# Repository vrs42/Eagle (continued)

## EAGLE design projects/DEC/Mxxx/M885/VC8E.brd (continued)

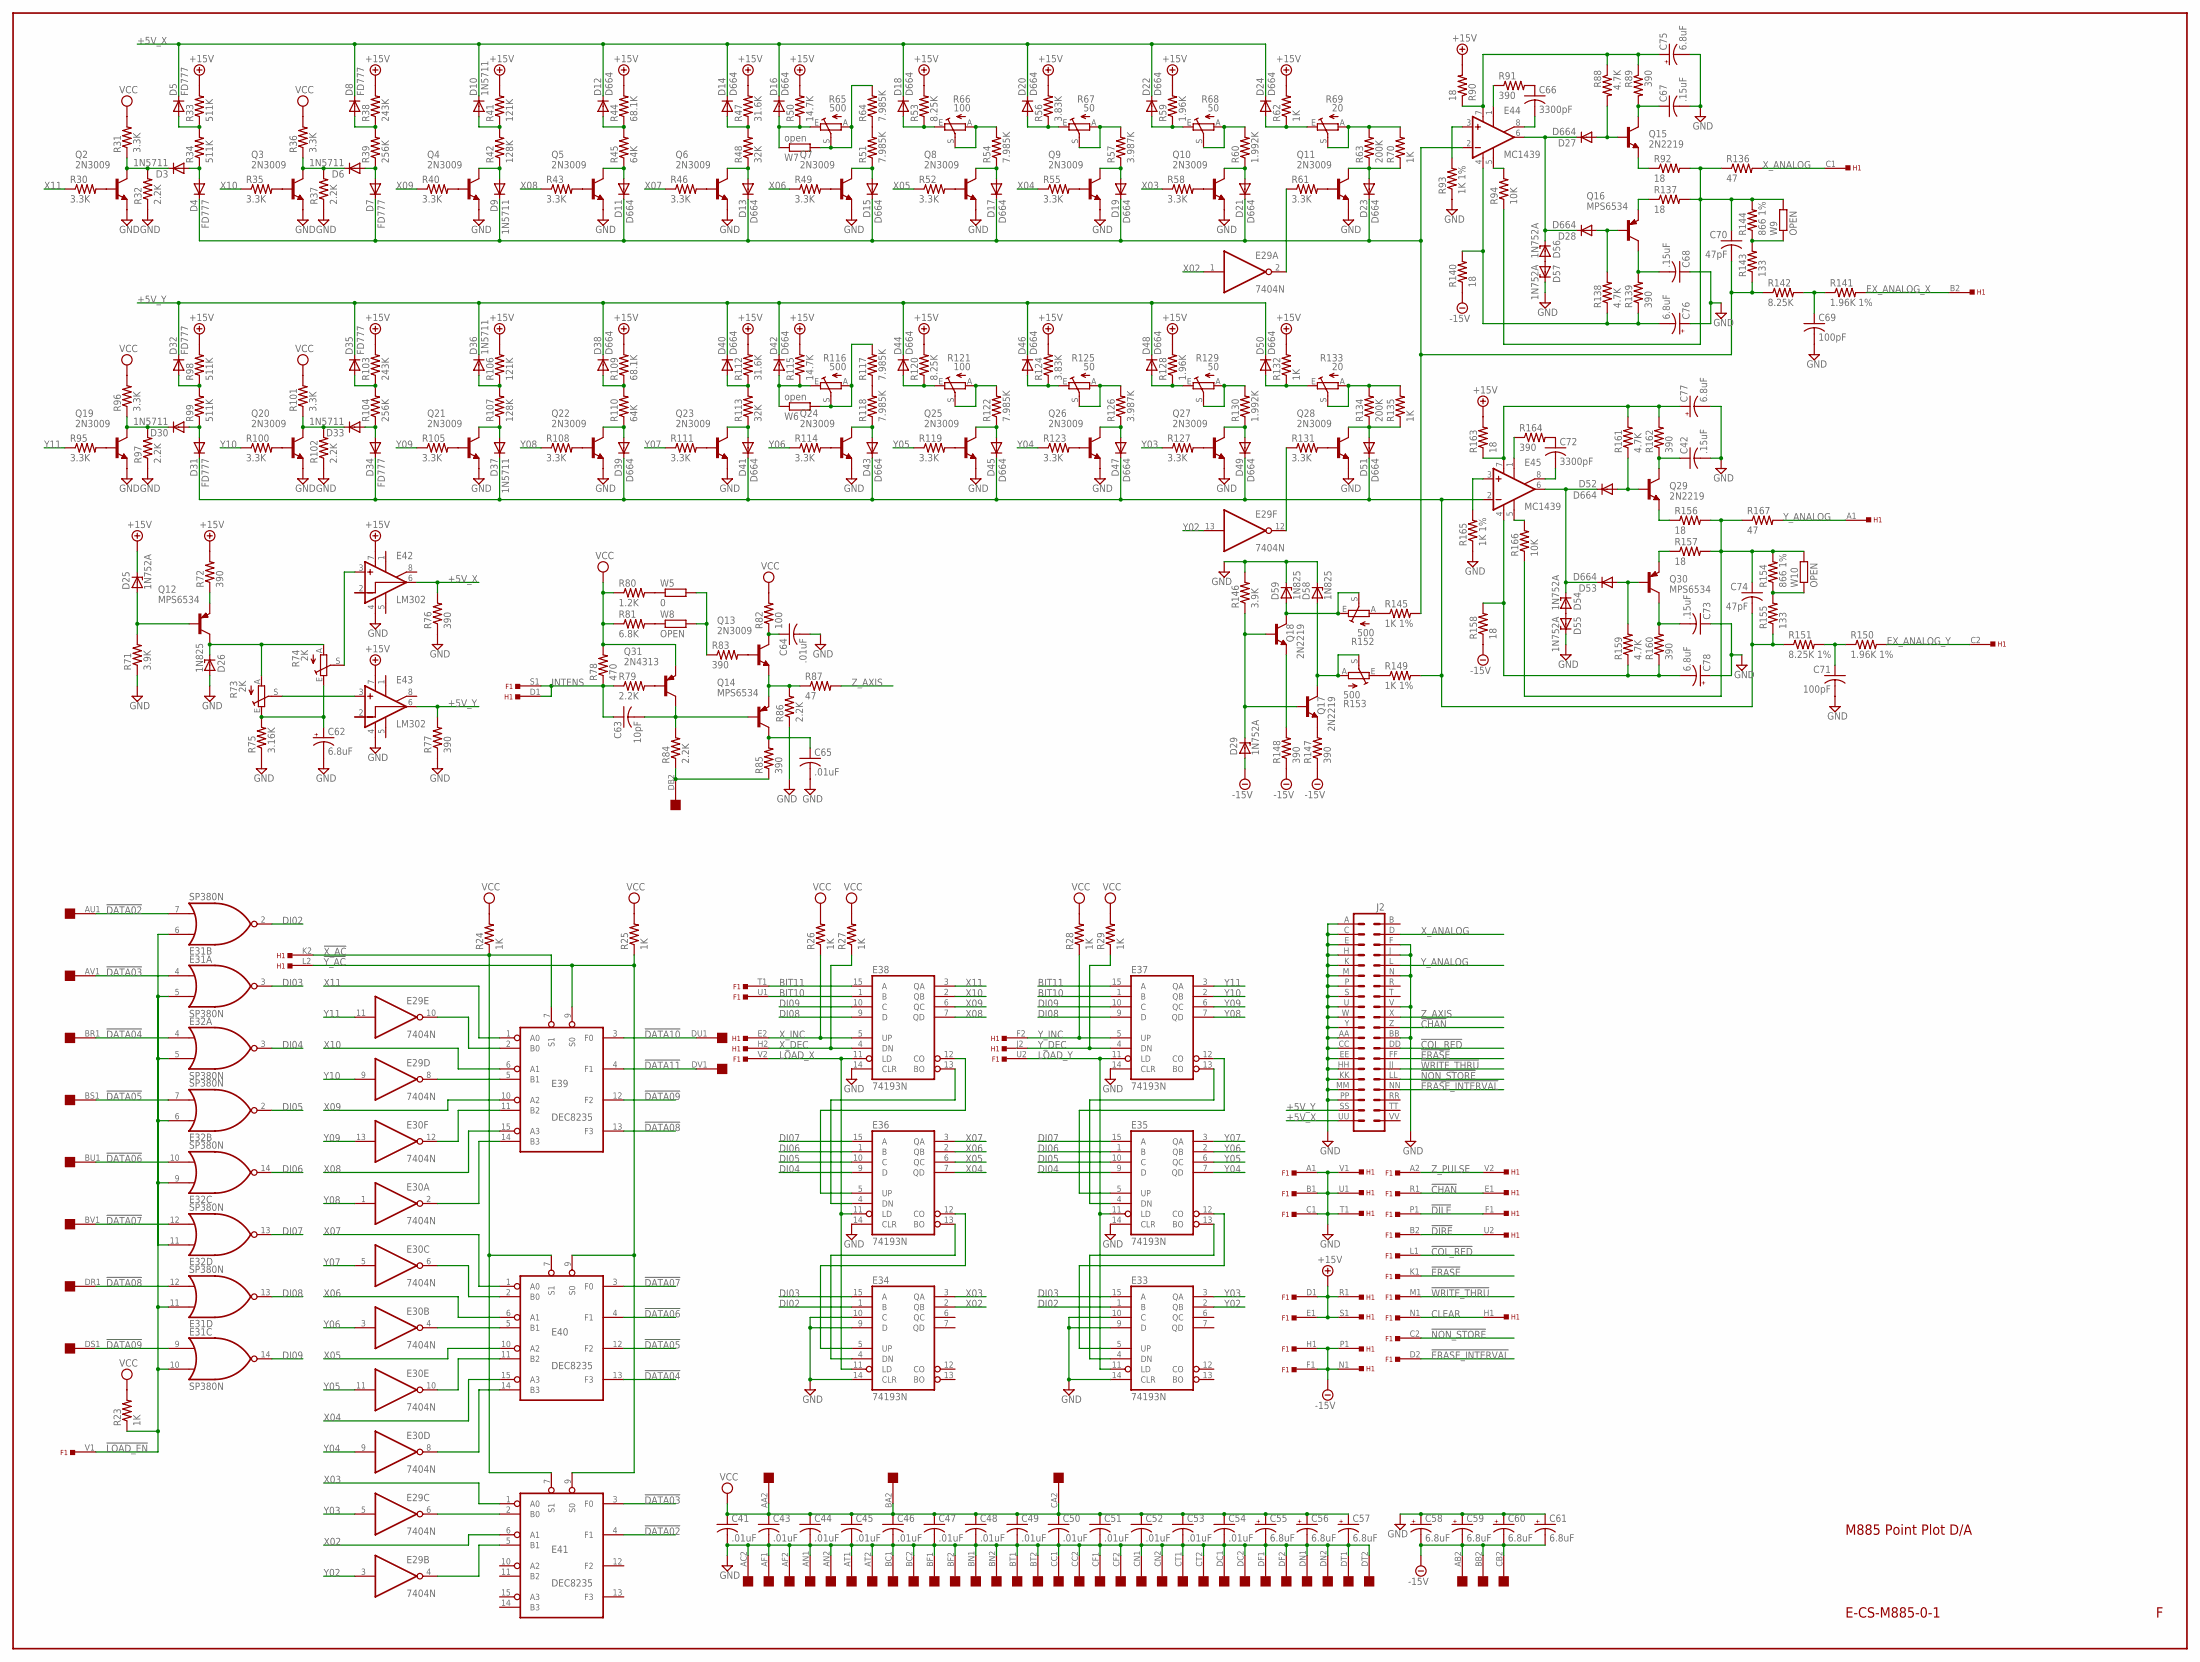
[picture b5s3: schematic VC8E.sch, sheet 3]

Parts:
C41, C43, C44, C45, C46, C47, C48, C49, C50, C51, C52, C53, C54, C64, C65: .01uF; C063-025X075
C42, C67, C68, C73: .15uF; C150-054X183
C55, C56, C57, C58, C59, C60, C61, C62, C75, C76, C77, C78: 6.8uF; E12-8
C63: 10pF; C063-025X075
C66, C72: 3300pF; C150-054X183
C69, C71: 100pF; C063-025X075
C70, C74: 47pF; C063-025X075
D3, D6, D9, D10, D30, D33, D36, D37: 1N5711; DO35-10
D4, D5, D7, D8, D31, D32, D34, D35: FD777; DO35-10
D11, D12, D13, D14, D15, D16, D17, D18, D19, D20, D21, D22, D23, D24, D27, D28, D38, D39, D40, D41, D42, D43, D44, D45, D46, D47, D48, D49, D50, D51, D52, D53: D664; DO35-10
D25, D29, D54, D55, D56, D57: 1N752A; DO35Z10
D26, D58, D59: 1N825; DO35Z10
E29, E30: 7404N; DIL14
E31, E32: SP380N; DIL14
E33, E34, E35, E36, E37, E38: 74193N; DIL16
E39, E40, E41: DEC8235; DIL16
E42, E43: LM302; TO99
E44, E45: MC1439; TO99
F1: EDGE-TOP; EDGE-CON2
H1: EDGE-TOP; EDGE-CON2
J2: DEC40PINH
OMNIBUS1: QUAD; EDGE-CON8
Q2, Q3, Q4, Q5, Q6, Q7, Q8, Q9, Q10, Q11, Q13, Q19, Q20, Q21, Q22, Q23, Q24, Q25, Q26, Q27, Q28: 2N3009; TO5
Q12, Q14, Q16, Q30: MPS6534; TO5
Q15, Q17, Q18, Q29: 2N2219; TO5
Q31: 2N4313; TO5
R23, R24, R25, R26, R27, R28, R29: 1K; 0207/10
R30, R31, R35, R36, R40, R43, R46, R49, R52, R55, R58, R61, R95, R96, R100, R101, R105, R108, R111, R114, R119, R123, R127, R131: 3.3K; 0207/10
R32, R37, R79, R84, R86, R97, R102: 2.2K; 0207/10
R33, R34, R98, R99: 511K; 0207/15
R38, R103: 243K; 0207/15
R39, R104: 256K; 0207/15
R41, R106: 121K; 0207/15
R42, R107: 128K; 0207/15
R44, R109: 68.1K; 0207/15
R45, R110: 64K; 0207/15
R47, R112: 31.6K; 0207/15
R48, R113: 32K; 0207/15
R50, R115: 14.7K; 0207/15
R51, R54, R64, R117, R118, R122: 7.985K; 0207/15
R53, R120, R142: 8.25K; 0207/15
R56, R124: 3.83K; 0207/15
R57, R126: 3.987K; 0207/15
R59, R128: 1.96K; 0207/15
R60, R130: 1.992K; 0207/15
R62, R70, R132, R135: 1K; 0207/15
R63, R134: 200K; 0207/15
R65, R116: 500; S75P
R66, R121: 100; S75P
R67, R68, R125, R129: 50; S75P
R69, R133: 20; S75P
R71, R146: 3.9K; 0207/10
R72, R76, R77, R83, R85, R89, R91, R139, R147, R148, R160, R162, R164: 390; 0207/10
R73, R74: 2K; SP19L
R75: 3.16K; 0207/15
R78: 470; 0207/10
R80: 1.2K; 0207/10
R81: 6.8K; 0207/10
R82: 100; 0207/10
R87, R136, R167: 47; 0207/10
R88, R138, R159, R161: 4.7K; 0207/10
R90, R92, R137, R140, R156, R157, R158, R163: 18; 0207/10
R93, R145, R149, R165: 1K 1%; 0207/15
R94, R166: 10K; 0207/10
R141, R150: 1.96K 1%; 0207/15
R143, R155: 133; 0207/15
R144, R154: 866 1%; 0207/15
R151: 8.25K 1%; 0207/10
R152, R153: 500; SP19L
W5: 0; 0207/10
W6, W7: open; 0207/10
W8, W9, W10: OPEN; 0207/10

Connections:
!CHAN: F1.R1, H1.E1, J2.Z (22); also elsewhere on the board
!COL_RED: F1.L1, J2.DD (26); also elsewhere on the board
!DATA02: E31.7 (I1), E41.4 (F1), OMNIBUS1.AU1
!DATA03: E31.4 (I0), E41.3 (F0), OMNIBUS1.AV1
!DATA04: E32.4 (I0), E40.13 (F3), OMNIBUS1.BR1
!DATA05: E32.7 (I1), E40.12 (F2), OMNIBUS1.BS1
!DATA06: E32.10 (I1), E40.4 (F1), OMNIBUS1.BU1; also elsewhere on the board
!DATA07: E32.12 (I1), E40.3 (F0), OMNIBUS1.BV1; also elsewhere on the board
!DATA08: E31.12 (I1), E39.13 (F3), OMNIBUS1.DR1; also elsewhere on the board
!DATA09: E31.9 (I0), E39.12 (F2), OMNIBUS1.DS1; also elsewhere on the board
!DATA10: E39.3 (F0), OMNIBUS1.DU1; also elsewhere on the board
!DATA11: E39.4 (F1), OMNIBUS1.DV1; also elsewhere on the board
!DILE: F1.P1, H1.F1; also elsewhere on the board
!DIRE: F1.B2, H1.U2; also elsewhere on the board
!ERASE: F1.K1, J2.FF (28); also elsewhere on the board
!ERASE_INTERVAL: F1.D2, J2.NN (34); also elsewhere on the board
!LOAD_EN: E31.5 (I1), E31.6 (I0), E31.10 (I1), E31.11 (I0), E32.5 (I1), E32.6 (I0), E32.9 (I0), E32.11 (I0), F1.V1, R23.1; also elsewhere on the board
!NON_STORE: F1.C2, J2.LL (32); also elsewhere on the board
!WRITE_THRU: F1.M1, J2.JJ (30); also elsewhere on the board
!X_AC: E39.7 (S1), E40.7 (S1), E41.7 (S1), H1.K2, R24.1
!Y_AC: E39.9 (S0), E40.9 (S0), E41.9 (S0), H1.L2, R25.1
+5V_X: D5.C, D8.C, D10.C, D12.C, D14.C, D16.C, D18.C, D20.C, D22.C, D24.C, E42.6 (OUT), J2.UU (39), R76.2
+5V_Y: D32.C, D35.C, D36.C, D38.C, D40.C, D42.C, D44.C, D46.C, D48.C, D50.C, E43.6 (OUT), J2.SS (37), R77.2
+15V: D25.C, E42.7 (V+), E43.7 (V+), F1.D1, F1.E1, H1.R1, H1.S1, R33.2, R38.2, R41.2, R44.2, R47.2, R50.2, R53.2, R56.2, R59.2, R62.2, R72.2, R90.2, R98.2, R103.2, R106.2, R109.2, R112.2, R115.2, R120.2, R124.2, R128.2, R132.2, R163.2; also elsewhere on the board
-15V: C58.-, C59.-, C60.-, C61.-, D29.A, F1.F1, F1.H1, H1.N1, H1.P1, OMNIBUS1.AB2, OMNIBUS1.BB2, OMNIBUS1.CB2, R140.1, R147.1, R148.1, R158.1; also elsewhere on the board
BIT10: E37.1 (B), E38.1 (B), F1.U1; also elsewhere on the board
BIT11: E37.15 (A), E38.15 (A), F1.T1; also elsewhere on the board
CLEAR: F1.N1, H1.H1; also elsewhere on the board
DI02: E31.2 (O), E33.1 (B), E34.1 (B)
DI03: E31.3 (O), E33.15 (A), E34.15 (A)
DI04: E32.3 (O), E35.9 (D), E36.9 (D)
DI05: E32.2 (O), E35.10 (C), E36.10 (C)
DI06: E32.14 (O), E35.1 (B), E36.1 (B)
DI07: E32.13 (O), E35.15 (A), E36.15 (A)
DI08: E31.13 (O), E37.9 (D), E38.9 (D)
DI09: E31.14 (O), E37.10 (C), E38.10 (C)
EX_ANALOG_X: H1.B2, R141.2
EX_ANALOG_Y: H1.C2, R150.2
GND: C41.2, C42.2, C43.2, C44.2, C45.2, C46.2, C47.2, C48.2, C49.2, C50.2, C51.2, C52.2, C53.2, C54.2, C55.-, C56.-, C57.-, C58.+, C59.+, C60.+, C61.+, C62.-, C64.2, C65.2, C67.2, C68.1, C69.2, C71.2, C73.1, C75.-, C76.+, C77.-, C78.+, D26.A, D55.C, D57.C, D58.C, D59.C, E29.7 (GND), E30.7 (GND), E31.1 (GND), E32.1 (GND), E33.8 (GND), E33.9 (D), E33.10 (C), E33.14 (CLR), E34.8 (GND), E34.9 (D), E34.10 (C), E34.14 (CLR), E35.8 (GND), E35.14 (CLR), E36.8 (GND), E36.14 (CLR), E37.8 (GND), E37.14 (CLR), E38.8 (GND), E38.14 (CLR), E39.8 (GND), E40.8 (GND), E41.8 (GND), E42.4 (V-), E43.4 (V-), F1.A1, F1.B1, F1.C1, H1.T1, H1.U1, H1.V1, J2.A (1), J2.AA (23), J2.BB (24), J2.C (3), J2.CC (25), J2.E (5), J2.EE (27), J2.F (6), J2.H (7), J2.HH (29), J2.J (8), J2.K (9), J2.KK (31), J2.M (11), J2.MM (33), J2.N (12), J2.P (13), J2.PP (35), J2.S (15), J2.U (17), J2.V (18), J2.W (19), J2.Y (21), OMNIBUS1.AC2, OMNIBUS1.AF1, OMNIBUS1.AF2, OMNIBUS1.AN1, OMNIBUS1.AN2, OMNIBUS1.AT1, OMNIBUS1.AT2, OMNIBUS1.BC1, OMNIBUS1.BC2, OMNIBUS1.BF1, OMNIBUS1.BF2, OMNIBUS1.BN1, OMNIBUS1.BN2, OMNIBUS1.BT1, OMNIBUS1.BT2, OMNIBUS1.CC1, OMNIBUS1.CC2, OMNIBUS1.CF1, OMNIBUS1.CF2, OMNIBUS1.CN1, OMNIBUS1.CN2, OMNIBUS1.CT1, OMNIBUS1.CT2, OMNIBUS1.DC1, OMNIBUS1.DC2, OMNIBUS1.DF1, OMNIBUS1.DF2, OMNIBUS1.DN1, OMNIBUS1.DN2, OMNIBUS1.DT1, OMNIBUS1.DT2, Q2.1 (E), Q3.1 (E), Q4.1 (E), Q5.1 (E), Q6.1 (E), Q7.1 (E), Q8.1 (E), Q9.1 (E), Q10.1 (E), Q11.1 (E), Q19.1 (E), Q20.1 (E), Q21.1 (E), Q22.1 (E), Q23.1 (E), Q24.1 (E), Q25.1 (E), Q26.1 (E), Q27.1 (E), Q28.1 (E), R32.1, R37.1, R71.1, R75.1, R76.1, R77.1, R86.1, R93.1, R97.1, R102.1, R146.2, R165.1; also elsewhere on the board
INTENS: C63.1, F1.S1, H1.D1, R78.1, R79.1; also elsewhere on the board
LOAD_X: E34.11 (LD), E36.11 (LD), E38.11 (LD), F1.V2; also elsewhere on the board
LOAD_Y: E33.11 (LD), E35.11 (LD), E37.11 (LD), F1.U2; also elsewhere on the board
unnamed: E29.10 (O), E39.2 (B0)
unnamed: E29.8 (O), E39.5 (B1)
unnamed: E30.12 (O), E39.11 (B2)
unnamed: E30.2 (O), E39.14 (B3)
unnamed: E30.6 (O), E40.2 (B0)
unnamed: E30.4 (O), E40.5 (B1)
unnamed: E30.10 (O), E40.11 (B2)
unnamed: E30.8 (O), E40.14 (B3)
unnamed: E29.6 (O), E41.2 (B0)
unnamed: E29.4 (O), E41.5 (B1)
unnamed: E34.4 (DN), E36.13 (BO)
unnamed: E34.5 (UP), E36.12 (CO)
unnamed: E36.4 (DN), E38.13 (BO)
unnamed: E36.5 (UP), E38.12 (CO)
unnamed: E33.4 (DN), E35.13 (BO)
unnamed: E33.5 (UP), E35.12 (CO)
unnamed: E35.4 (DN), E37.13 (BO)
unnamed: E35.5 (UP), E37.12 (CO)
unnamed: D5.A, R33.1, R34.2
unnamed: D3.A, D4.A, R34.1
unnamed: Q2.2 (B), R30.2
unnamed: D3.C, Q2.3 (C), R31.1, R32.2
unnamed: D8.A, R38.1, R39.2
unnamed: D6.A, D7.A, R39.1
unnamed: Q3.2 (B), R35.2
unnamed: D6.C, Q3.3 (C), R36.1, R37.2
unnamed: D10.A, R41.1, R42.2
unnamed: D9.A, Q4.3 (C), R42.1
unnamed: Q4.2 (B), R40.2
unnamed: D12.A, R44.1, R45.2
unnamed: D11.A, Q5.3 (C), R45.1
unnamed: Q5.2 (B), R43.2
unnamed: D14.A, R47.1, R48.2
unnamed: D13.A, Q6.3 (C), R48.1
unnamed: Q6.2 (B), R46.2
unnamed: D15.A, Q7.3 (C), R51.1
unnamed: Q7.2 (B), R49.2
unnamed: D18.A, R53.1, R66.E
unnamed: D17.A, Q8.3 (C), R54.1
unnamed: Q8.2 (B), R52.2
unnamed: R57.2, R67.A, R67.S
unnamed: D19.A, Q9.3 (C), R57.1
unnamed: Q9.2 (B), R55.2
unnamed: D22.A, R59.1, R68.E
unnamed: D21.A, Q10.3 (C), R60.1
unnamed: Q10.2 (B), R58.2
unnamed: D24.A, R62.1, R69.E
unnamed: D23.A, Q11.3 (C), R63.1, R70.1
unnamed: Q11.2 (B), R61.2
unnamed: E29.2 (O), R61.1
unnamed: D16.A, R50.1, R65.E, W7.1
unnamed: R51.2, R64.1
unnamed: R64.2, R65.A, R65.S, W7.2
unnamed: R54.2, R66.A, R66.S
unnamed: D20.A, R56.1, R67.E
unnamed: R60.2, R68.A, R68.S
unnamed: R63.2, R69.A, R69.S, R70.2
unnamed: D32.A, R98.1, R99.2
unnamed: D30.A, D31.A, R99.1
unnamed: Q19.2 (B), R95.2
unnamed: D30.C, Q19.3 (C), R96.1, R97.2
unnamed: D35.A, R103.1, R104.2
unnamed: D33.A, D34.A, R104.1
unnamed: C74.2, D31.C, D34.C, D37.C, D39.C, D41.C, D43.C, D45.C, D47.C, D49.C, D51.C, E45.2 (-IN), R149.2, R151.1, R155.1
unnamed: Q20.2 (B), R100.2
unnamed: D33.C, Q20.3 (C), R101.1, R102.2
unnamed: D36.A, R106.1, R107.2
unnamed: D37.A, Q21.3 (C), R107.1
unnamed: Q21.2 (B), R105.2
unnamed: D38.A, R109.1, R110.2
unnamed: D39.A, Q22.3 (C), R110.1
unnamed: Q22.2 (B), R108.2
unnamed: D40.A, R112.1, R113.2
unnamed: D41.A, Q23.3 (C), R113.1
unnamed: Q23.2 (B), R111.2
unnamed: D43.A, Q24.3 (C), R118.1
unnamed: Q24.2 (B), R114.2
unnamed: D44.A, R120.1, R121.E
unnamed: D45.A, Q25.3 (C), R122.1
unnamed: Q25.2 (B), R119.2
unnamed: R125.A, R125.S, R126.2
unnamed: D47.A, Q26.3 (C), R126.1
unnamed: Q26.2 (B), R123.2
unnamed: D48.A, R128.1, R129.E
unnamed: D49.A, Q27.3 (C), R130.1
unnamed: Q27.2 (B), R127.2
unnamed: D50.A, R132.1, R133.E
unnamed: D51.A, Q28.3 (C), R134.1, R135.1
unnamed: Q28.2 (B), R131.2
unnamed: E29.12 (O), R131.1
unnamed: D42.A, R115.1, R116.E, W6.1
unnamed: R117.1, R118.2
unnamed: R116.A, R116.S, R117.2, W6.2
unnamed: R121.A, R121.S, R122.2
unnamed: D46.A, R124.1, R125.E
unnamed: R129.A, R129.S, R130.2
unnamed: R133.A, R133.S, R134.2, R135.2
unnamed: D25.A, Q12.2 (B), R71.2
unnamed: Q12.1 (E), R72.1
unnamed: D26.C, Q12.3 (C), R73.A, R74.A
unnamed: C62.+, R73.E, R74.E, R75.2
unnamed: E43.3 (+IN), R73.S
unnamed: E42.3 (+IN), R74.S
unnamed: Q31.2 (B), R79.2
unnamed: C63.2, Q14.2 (B), Q31.3 (C), R84.2
unnamed: OMNIBUS1.DB2, R84.1, R85.1
unnamed: C65.1, Q14.3 (C), R85.2
unnamed: Q13.1 (E), Q14.1 (E), R86.2, R87.1
unnamed: R80.2, W5.1
unnamed: R81.2, W8.1
unnamed: Q13.2 (B), R83.2
unnamed: R83.1, W5.2, W8.2
unnamed: C64.1, Q13.3 (C), R82.1
unnamed: C75.+, E44.7 (V+), R88.1, R89.1, R90.1
unnamed: C66.1, R91.2
unnamed: C66.2, E44.8 (ON2)
unnamed: E44.1 (ON1), R91.1
unnamed: D27.C, D28.C, D56.C, E44.6 (OUT)
unnamed: D56.A, D57.A
unnamed: D27.A, Q15.2 (B), R88.2
unnamed: C67.1, Q15.3 (C), R89.2
unnamed: D28.A, Q16.2 (B), R138.2
unnamed: C68.2, Q16.3 (C), R139.2
unnamed: C76.-, E44.4 (V-), R138.1, R139.1, R140.2
unnamed: E44.5 (OPT), R94.2
unnamed: C70.1, R92.2, R94.1, R136.1, R137.2, R144.2, W9.2
unnamed: Q16.1 (E), R137.1
unnamed: Q15.1 (E), R92.1
unnamed: E44.3 (+IN), R93.2
unnamed: R143.2, R144.1, W9.1
unnamed: C70.2, D4.C, D7.C, D9.C, D11.C, D13.C, D15.C, D17.C, D19.C, D21.C, D23.C, E44.2 (-IN), R142.1, R143.1, R145.2
unnamed: C69.1, R141.1, R142.2
unnamed: R145.1, R152.A
unnamed: D29.C, Q17.2 (B), Q18.2 (B), R146.1
unnamed: Q18.1 (E), R148.2
unnamed: Q17.1 (E), R147.2
unnamed: D59.A, Q18.3 (C), R152.E, R152.S
unnamed: D58.A, Q17.3 (C), R153.A, R153.S
unnamed: R149.1, R153.E
unnamed: C77.+, E45.7 (V+), R161.2, R162.2, R163.1
unnamed: C72.2, E45.8 (ON2)
unnamed: E45.1 (ON1), R164.1
unnamed: D52.C, D53.C, D54.C, E45.6 (OUT)
unnamed: D52.A, Q29.2 (B), R161.1
unnamed: C42.1, Q29.3 (C), R162.1
unnamed: D53.A, Q30.2 (B), R159.2
unnamed: C73.2, Q30.3 (C), R160.2
unnamed: C78.-, E45.4 (V-), R158.2, R159.1, R160.1
unnamed: E45.5 (OPT), R166.2
unnamed: C74.1, R154.2, R156.2, R157.2, R166.1, R167.1, W10.2
unnamed: Q30.1 (E), R157.1
unnamed: Q29.1 (E), R156.1
unnamed: E45.3 (+IN), R165.2
unnamed: R154.1, R155.2, W10.1
unnamed: C71.1, R150.1, R151.2
unnamed: D54.A, D55.A
unnamed: C72.1, R164.2
VCC: C41.1, C43.1, C44.1, C45.1, C46.1, C47.1, C48.1, C49.1, C50.1, C51.1, C52.1, C53.1, C54.1, C55.+, C56.+, C57.+, E29.14 (VCC), E30.14 (VCC), E31.8 (VCC), E32.8 (VCC), E33.16 (VCC), E34.16 (VCC), E35.16 (VCC), E36.16 (VCC), E37.16 (VCC), E38.16 (VCC), E39.16 (VCC), E40.16 (VCC), E41.16 (VCC), OMNIBUS1.AA2, OMNIBUS1.BA2, OMNIBUS1.CA2, Q31.1 (E), R23.2, R24.2, R25.2, R26.2, R27.2, R28.2, R29.2, R31.2, R36.2, R78.2, R80.1, R81.1, R82.2, R96.2, R101.2; also elsewhere on the board
X02: E29.1 (I), E34.2 (QB), E41.6 (A1)
X03: E34.3 (QA), E41.1 (A0), R58.1
X04: E36.7 (QD), E40.15 (A3), R55.1
X05: E36.6 (QC), E40.10 (A2), R52.1
X06: E36.2 (QB), E40.6 (A1), R49.1
X07: E36.3 (QA), E40.1 (A0), R46.1
X08: E38.7 (QD), E39.15 (A3), R43.1
X09: E38.6 (QC), E39.10 (A2), R40.1
X10: E38.2 (QB), E39.6 (A1), R35.1
X11: E38.3 (QA), E39.1 (A0), R30.1
X_ANALOG: H1.C1, J2.D (4), R136.2
X_DEC: E38.4 (DN), H1.H2, R27.1
X_INC: E38.5 (UP), H1.E2, R26.1
Y02: E29.3 (I), E29.13 (I), E33.2 (QB)
Y03: E29.5 (I), E33.3 (QA), R127.1
Y04: E30.9 (I), E35.7 (QD), R123.1
Y05: E30.11 (I), E35.6 (QC), R119.1
Y06: E30.3 (I), E35.2 (QB), R114.1
Y07: E30.5 (I), E35.3 (QA), R111.1
Y08: E30.1 (I), E37.7 (QD), R108.1
Y09: E30.13 (I), E37.6 (QC), R105.1
Y10: E29.9 (I), E37.2 (QB), R100.1
Y11: E29.11 (I), E37.3 (QA), R95.1
Y_ANALOG: H1.A1, J2.L (10), R167.2
Y_DEC: E37.4 (DN), H1.J2, R29.1
Y_INC: E37.5 (UP), H1.F2, R28.1
Z_AXIS: J2.X (20), R87.2
Z_PULSE: F1.A2, H1.V2; also elsewhere on the board

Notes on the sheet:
E-CS-M885-0-1
M885 Point Plot D/A

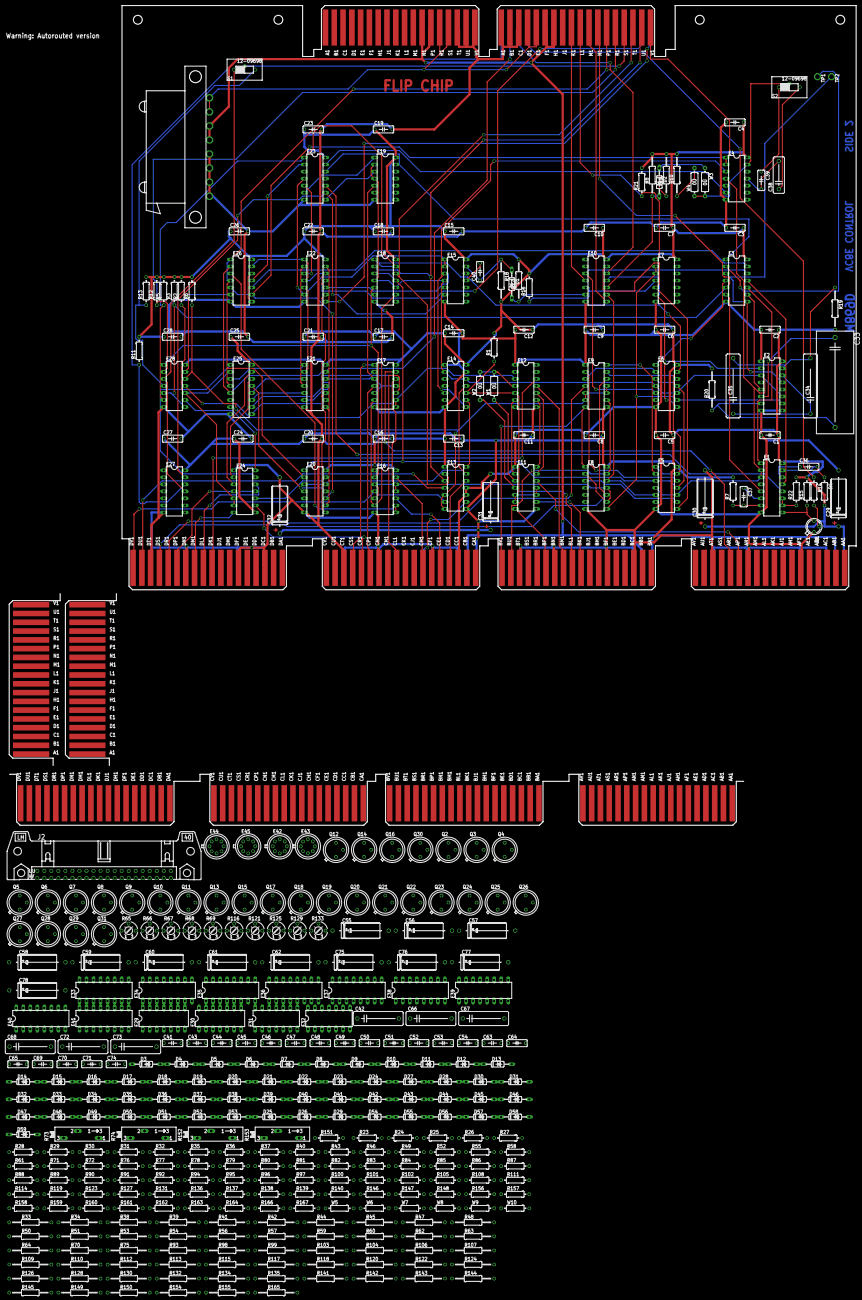
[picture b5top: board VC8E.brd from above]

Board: 4 copper layers, 306.1 x 296.2 mm, 402 parts (0 on the bottom side), 334 nets.

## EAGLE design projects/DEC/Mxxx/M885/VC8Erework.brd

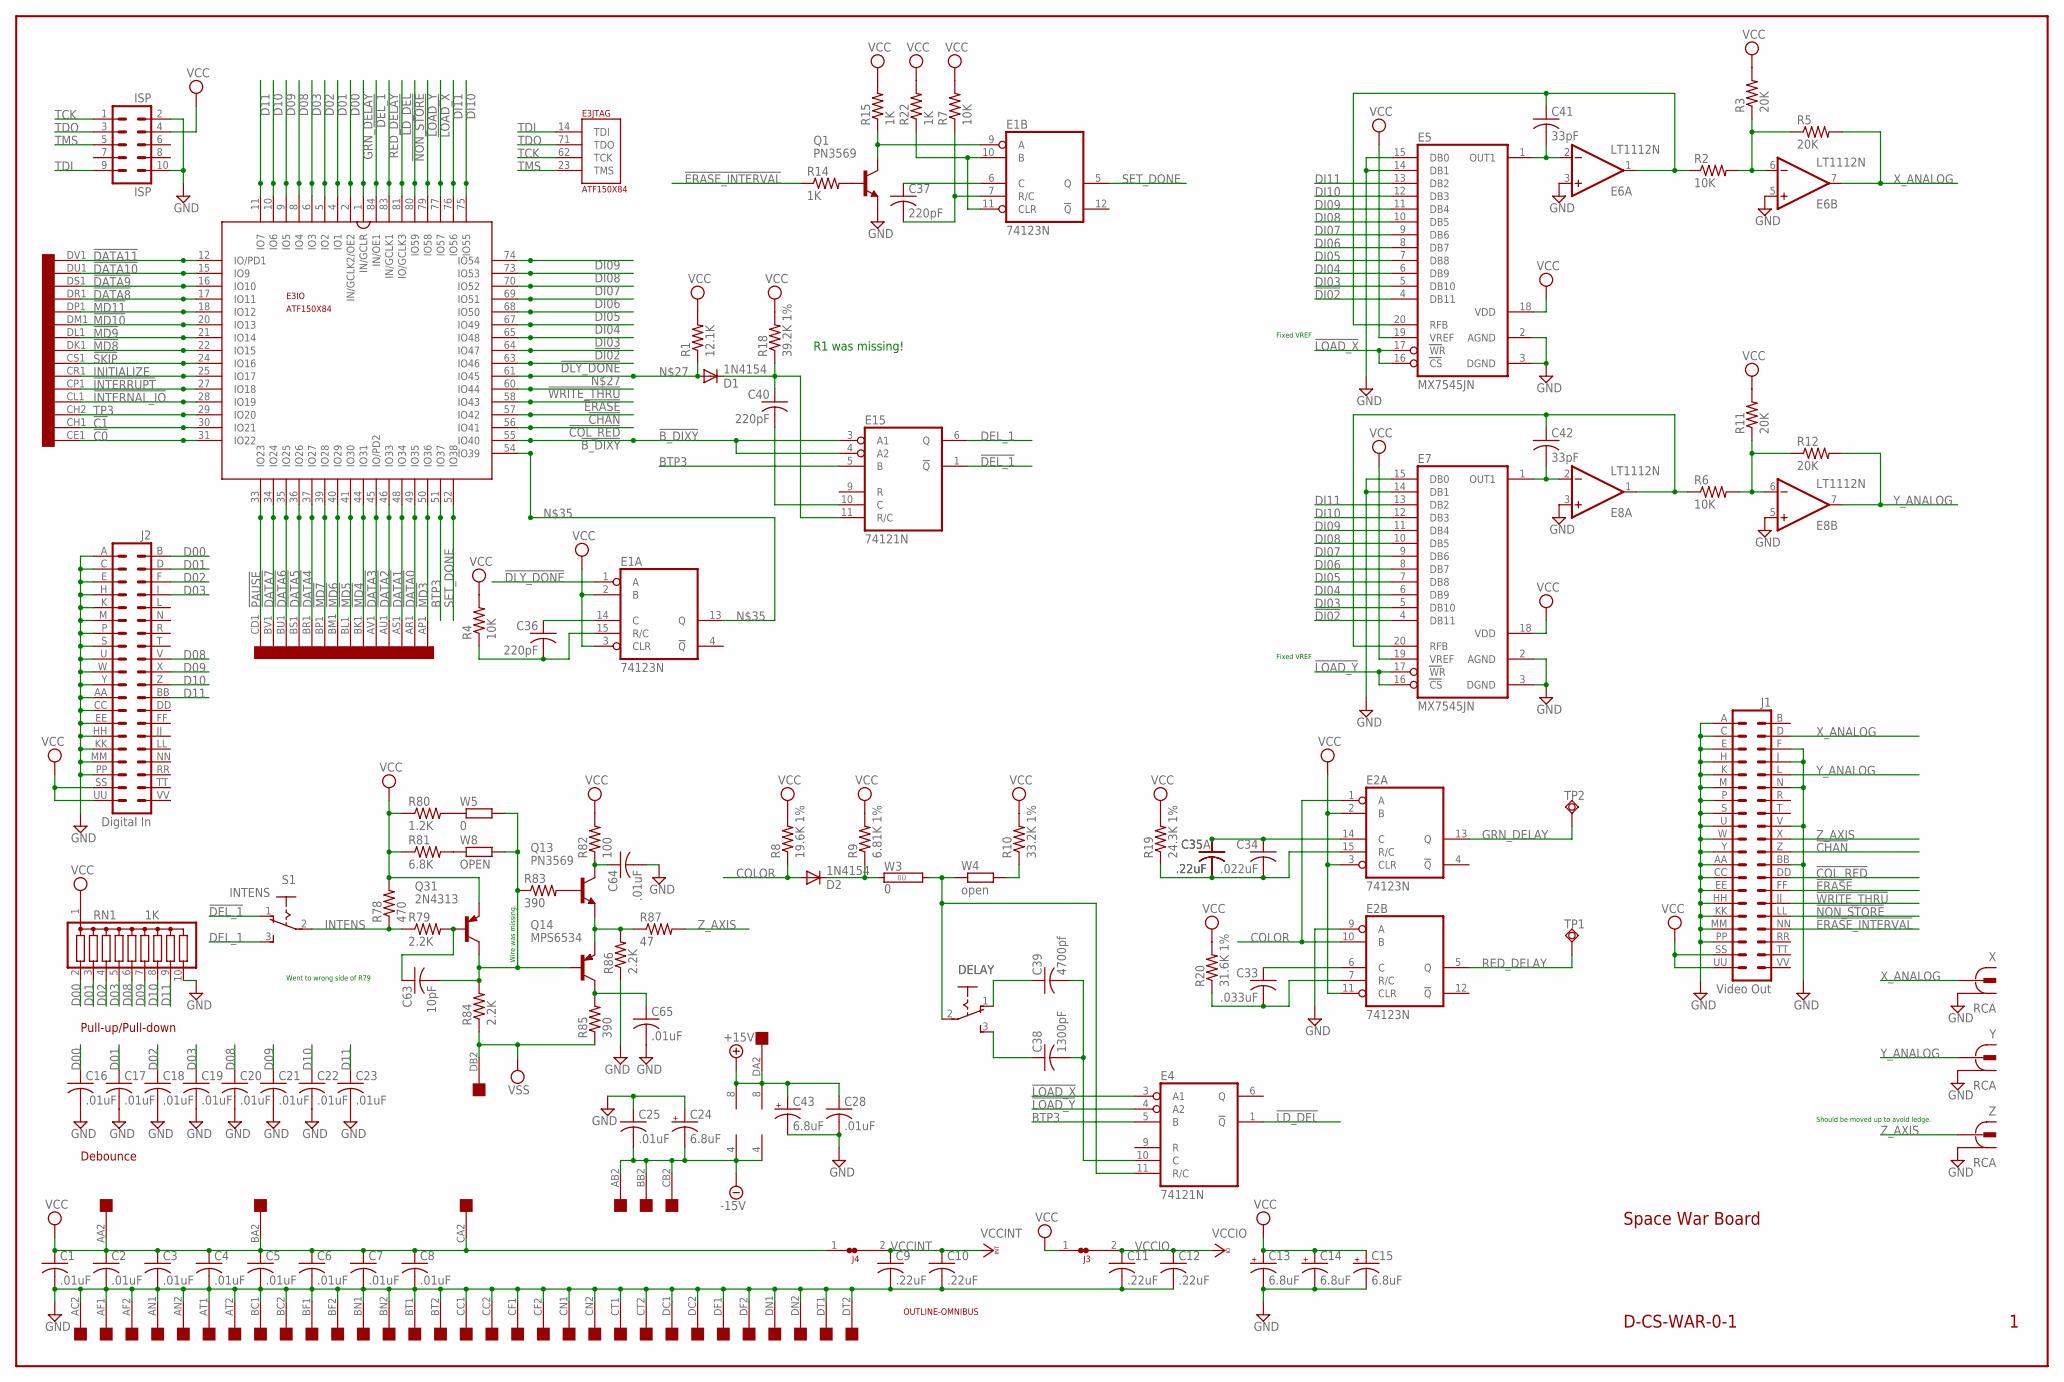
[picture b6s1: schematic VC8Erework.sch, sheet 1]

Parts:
C1, C2, C3, C4, C5, C6, C7, C8, C16, C17, C18, C19, C20, C21, C22, C23, C25, C28, C64, C65: .01uF; C063-025X075
C9, C10, C11, C12: .22uF; C063-025X075
C13, C14, C15, C24, C43: 6.8uF; E12-8
C33: .033uF; C102-043X133
C34: .022uF; C102-043X133
C35: .22uF; C050-025X075
C35A: .22uF; C102-043X133
C36, C37, C40: 220pF; C063-025X075
C38: 1300pF; C150-054X183
C39: 4700pf; C102-043X133
C41, C42: 33pF; C063-025X075
C63: 10pF; C063-025X075
D1, D2: 1N4154; DO35-10
DELAY: DELAY; M251
E1, E2: 74123N; DIL16
E3: ATF150X84; S84
E4, E15: 74121N; DIL14
E5, E7: MX7545JN; DIL20
E6, E8: LT1112N; DIL08
ISP: ISP; ML10
J1: Video Out; DEC40PINH
J2: Digital In; DEC40PINH
J3, J4: JUMPER-NC1; NC1
OMNIBUS: QUAD; EDGE-CON8
Q1: PN3569; TO18-
Q13: PN3569; TO5
Q14: MPS6534; TO5
Q31: 2N4313; TO5
R1: 12.1K; 0207/7
R2, R4, R6, R7: 10K; 0207/10
R3, R5, R11, R12: 20K; 0207/10
R8: 19.6K 1%; 0207/15
R9: 6.81K 1%; 0207/15
R10: 33.2K 1%; 0207/15
R14, R15, R22: 1K; 0207/10
R18: 39.2K 1%; 0207/15
R19: 24.3K 1%; 0207/15
R20: 31.6K 1%; 0207/15
R78: 470; 0207/10
R79, R84, R86: 2.2K; 0207/10
R80: 1.2K; 0207/10
R81: 6.8K; 0207/10
R82: 100; 0207/10
R83, R85: 390; 0207/10
R87: 47; 0207/10
RN1: 1K; SIL10
S1: INTENS; M251
TP1, TP2: TPSQPAD1-17; P1-17
U$1: OUTLINE-OMNIBUS; OMNIBUS
W3: 0; 0R/10
W4: open; 0207/10
W5: 0; 0207/10
W8: OPEN; 0207/10
X: RCA
Y: RCA
Z: RCA

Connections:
!B_DIXY: E3.55 (IO40), E15.3 (A1), E15.4 (A2)
!C0: E3.31 (IO22), OMNIBUS.CE1
!C1: E3.30 (IO21), OMNIBUS.CH1
!CHAN: E3.57 (IO42), J1.Z (22)
!COL_RED: E3.56 (IO41), J1.DD (26)
!DATA0: E3.49 (IO35), OMNIBUS.AR1
!DATA1: E3.48 (IO34), OMNIBUS.AS1
!DATA2: E3.46 (IO33), OMNIBUS.AU1
!DATA3: E3.45 (IO/PD2), OMNIBUS.AV1
!DATA4: E3.37 (IO27), OMNIBUS.BR1
!DATA5: E3.36 (IO26), OMNIBUS.BS1
!DATA6: E3.35 (IO25), OMNIBUS.BU1
!DATA7: E3.34 (IO24), OMNIBUS.BV1
!DATA8: E3.17 (IO11), OMNIBUS.DR1
!DATA9: E3.16 (IO10), OMNIBUS.DS1
!DATA10: E3.15 (IO9), OMNIBUS.DU1
!DATA11: E3.12 (IO/PD1), OMNIBUS.DV1
!DEL_1: E3.84 (IN/OE1), E15.1 (!Q), S1.1 (O)
!DI02: E3.64 (IO47), E5.4 (DB11), E7.4 (DB11)
!DLY_DONE: E1.1 (A), E3.63 (IO46)
!ERASE: E3.58 (IO43), J1.FF (28)
!ERASE_INTERVAL: J1.NN (34), R14.1
!INTERNAL_IO: E3.28 (IO19), OMNIBUS.CL1
!INTERRUPT: E3.27 (IO18), OMNIBUS.CP1
!LD_DEL: E3.81 (IO/GCLK3), E4.1 (!Q)
!LOAD_X: E3.77 (IO57), E4.3 (A1), E5.16 (CS), E5.17 (WR)
!LOAD_Y: E3.79 (IO58), E4.4 (A2), E7.16 (CS), E7.17 (WR)
!MD3: E3.50 (IO36), OMNIBUS.AP1
!MD4: E3.44 (IO31), OMNIBUS.BK1
!MD5: E3.41 (IO30), OMNIBUS.BL1
!MD6: E3.40 (IO29), OMNIBUS.BM1
!MD7: E3.39 (IO28), OMNIBUS.BP1
!MD8: E3.22 (IO15), OMNIBUS.DK1
!MD9: E3.21 (IO14), OMNIBUS.DL1
!MD10: E3.20 (IO13), OMNIBUS.DM1
!MD11: E3.18 (IO12), OMNIBUS.DP1
!NON_STORE: E3.80 (IO59), J1.LL (32)
!PAUSE: E3.33 (IO23), OMNIBUS.CD1
!SKIP: E3.24 (IO16), OMNIBUS.CS1
!WRITE_THRU: E3.60 (IO44), J1.JJ (30)
+15V: C28.1, C43.+, E6.8 (V+), E8.8 (V+), OMNIBUS.DA2
-15V: C24.-, C25.2, E6.4 (V-), E8.4 (V-), OMNIBUS.AB2, OMNIBUS.BB2, OMNIBUS.CB2
BTP3: E3.51 (IO37), E4.5 (B), E15.5 (B)
COLOR: D2.A, E2.1 (A), E2.10 (B), R8.1
D00: C16.1, E3.2 (IN/GCLK2/OE2), J2.B (2), RN1.2
D01: C17.1, E3.4 (IO1), J2.D (4), RN1.3
D02: C18.1, E3.5 (IO2), J2.F (6), RN1.4
D03: C19.1, E3.6 (IO3), J2.J (8), RN1.5
D08: C20.1, E3.8 (IO4), J2.V (18), RN1.6
D09: C21.1, E3.9 (IO5), J2.X (20), RN1.7
D10: C22.1, E3.10 (IO6), J2.Z (22), RN1.8
D11: C23.1, E3.11 (IO7), J2.BB (24), RN1.9
DEL_1: E15.6 (Q), S1.3 (S)
DI03: E3.65 (IO48), E5.5 (DB10), E7.5 (DB10)
DI04: E3.67 (IO49), E5.6 (DB9), E7.6 (DB9)
DI05: E3.68 (IO50), E5.7 (DB8), E7.7 (DB8)
DI06: E3.69 (IO51), E5.8 (DB7), E7.8 (DB7)
DI07: E3.70 (IO52), E5.9 (DB6), E7.9 (DB6)
DI08: E3.73 (IO53), E5.10 (DB5), E7.10 (DB5)
DI09: E3.74 (IO54), E5.11 (DB4), E7.11 (DB4)
DI10: E3.75 (IO55), E5.12 (DB3), E7.12 (DB3)
DI11: E3.76 (IO56), E5.13 (DB2), E7.13 (DB2)
GND: C1.2, C2.2, C3.2, C4.2, C5.2, C6.2, C7.2, C8.2, C9.2, C10.2, C11.2, C12.2, C13.-, C14.-, C15.-, C16.2, C17.2, C18.2, C19.2, C20.2, C21.2, C22.2, C23.2, C24.+, C25.1, C28.2, C43.-, C64.2, C65.2, E1.8 (GND), E2.8 (GND), E2.9 (A), E3.7 (GND), E3.19 (GND), E3.32 (GND), E3.42 (GND), E3.47 (GND), E3.59 (GND), E3.72 (GND), E3.82 (GND), E4.7 (GND), E5.2 (AGND), E5.3 (DGND), E5.14 (DB1), E5.15 (DB0), E6.3 (+IN), E6.5 (+IN), E7.2 (AGND), E7.3 (DGND), E7.14 (DB1), E7.15 (DB0), E8.3 (+IN), E8.5 (+IN), E15.7 (GND), ISP.2, ISP.10, J1.A (1), J1.AA (23), J1.BB (24), J1.C (3), J1.CC (25), J1.E (5), J1.EE (27), J1.F (6), J1.H (7), J1.HH (29), J1.J (8), J1.K (9), J1.KK (31), J1.M (11), J1.MM (33), J1.N (12), J1.P (13), J1.PP (35), J1.S (15), J1.U (17), J1.V (18), J1.W (19), J1.Y (21), J2.A (1), J2.AA (23), J2.C (3), J2.CC (25), J2.E (5), J2.EE (27), J2.H (7), J2.HH (29), J2.K (9), J2.KK (31), J2.M (11), J2.MM (33), J2.P (13), J2.PP (35), J2.S (15), J2.U (17), J2.W (19), J2.Y (21), OMNIBUS.AC2, OMNIBUS.AF1, OMNIBUS.AF2, OMNIBUS.AN1, OMNIBUS.AN2, OMNIBUS.AT1, OMNIBUS.AT2, OMNIBUS.BC1, OMNIBUS.BC2, OMNIBUS.BF1, OMNIBUS.BF2, OMNIBUS.BN1, OMNIBUS.BN2, OMNIBUS.BT1, OMNIBUS.BT2, OMNIBUS.CC1, OMNIBUS.CC2, OMNIBUS.CF1, OMNIBUS.CF2, OMNIBUS.CN1, OMNIBUS.CN2, OMNIBUS.CT1, OMNIBUS.CT2, OMNIBUS.DC1, OMNIBUS.DC2, OMNIBUS.DF1, OMNIBUS.DF2, OMNIBUS.DN1, OMNIBUS.DN2, OMNIBUS.DT1, OMNIBUS.DT2, Q1.1 (E), R86.1, RN1.10, X.1, X.1@1 (1), X.1@2 (1), Y.1, Y.1@1 (1), Y.1@2 (1), Z.1, Z.1@1 (1), Z.1@2 (1)
GRN_DELAY: E2.13 (Q), E3.1 (IN/GCLR), TP2.TP
INITIALIZE: E3.25 (IO17), OMNIBUS.CR1
INTENS: R78.1, R79.1, S1.2
unnamed: C41.2, E5.1 (OUT1), E6.2 (-IN)
unnamed: E6.6 (-IN), R2.2, R3.1, R5.1
unnamed: C41.1, E5.20 (RFB), E6.1 (OUT), R2.1
unnamed: C39.1, DELAY.1 (O)
unnamed: C42.2, E7.1 (OUT1), E8.2 (-IN)
unnamed: E8.6 (-IN), R6.2, R11.1, R12.1
unnamed: C42.1, E7.20 (RFB), E8.1 (OUT), R6.1
unnamed: D1.A, E3.61 (IO45), R1.1
unnamed: C40.1, D1.C, E15.11 (R/C), R18.1
unnamed: C40.2, E15.10 (C)
unnamed: C34.2, C35.2, C35A.2, E2.15 (R/C), R19.1
unnamed: C33.2, E2.7 (R/C), R20.1
unnamed: C33.1, E2.6 (C)
unnamed: C34.1, C35.1, C35A.1, E2.14 (C)
unnamed: E1.13 (Q), E3.54 (IO39)
unnamed: C36.2, E1.15 (R/C), R4.1
unnamed: C36.1, E1.14 (C)
unnamed: Q1.2 (B), R14.2
unnamed: E1.9 (A), Q1.3 (C), R15.1
unnamed: E1.10 (B), E1.11 (CLR), R22.1
unnamed: C37.2, E1.7 (R/C), R7.1
unnamed: C37.1, E1.6 (C)
unnamed: D2.C, R9.1, W3.1
unnamed: DELAY.2, E4.11 (R/C), W3.2, W4.1
unnamed: R10.1, W4.2
unnamed: C38.1, DELAY.3 (S)
unnamed: C38.2, C39.2, E4.10 (C)
unnamed: C63.1, Q31.2 (B), R79.2
unnamed: C63.2, Q14.2 (B), Q31.3 (C), R83.1, R84.2, W5.2, W8.2
unnamed: C65.1, Q14.3 (C), R85.2
unnamed: Q13.1 (E), Q14.1 (E), R86.2, R87.1
unnamed: R80.2, W5.1
unnamed: R81.2, W8.1
unnamed: Q13.2 (B), R83.2
unnamed: C64.1, Q13.3 (C), R82.1
RED_DELAY: E2.5 (Q), E3.83 (IN/GCLK1), TP1.TP
SET_DONE: E1.5 (Q), E3.52 (IO38)
TCK: E3.62 (TCK), ISP.1
TDI: E3.14 (TDI), ISP.9
TDO: E3.71 (TDO), ISP.3
TMS: E3.23 (TMS), ISP.5
TP3: E3.29 (IO20), OMNIBUS.CH2
VCC: C1.1, C2.1, C3.1, C4.1, C5.1, C6.1, C7.1, C8.1, C13.+, C14.+, C15.+, E1.2 (B), E1.3 (CLR), E1.16 (VCC), E2.2 (B), E2.3 (CLR), E2.11 (CLR), E2.16 (VCC), E4.14 (VCC), E5.18 (VDD), E5.19 (VREF), E7.18 (VDD), E7.19 (VREF), E15.14 (VCC), ISP.4, J1.SS (37), J1.UU (39), J2.SS (37), J2.UU (39), J3.1, J4.1, OMNIBUS.AA2, OMNIBUS.BA2, OMNIBUS.CA2, Q31.1 (E), R1.2, R3.2, R4.2, R7.2, R8.2, R9.2, R10.2, R11.2, R15.2, R18.2, R19.2, R20.2, R22.2, R78.2, R80.1, R81.1, R82.2, RN1.1
VCCINT: C9.1, C10.1, E3.3 (VCCINT), E3.43 (VCCINT), J4.2
VCCIO: C11.1, C12.1, E3.13 (VCCIO), E3.26 (VCCIO), E3.38 (VCCIO), E3.53 (VCCIO), E3.66 (VCCIO), E3.78 (VCCIO), J3.2
VSS: OMNIBUS.DB2, R84.1, R85.1
X_ANALOG: E6.7 (OUT), J1.D (4), R5.2, X.2
Y_ANALOG: E8.7 (OUT), J1.L (10), R12.2, Y.2
Z_AXIS: J1.X (20), R87.2, Z.2

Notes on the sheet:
D-CS-WAR-0-1
Space War Board
Debounce
Pull-up/Pull-down
Went to wrong side of R79
Fixed VREF
Should be moved up to avoid ledge.
R1 was missing!
Wire was missing.

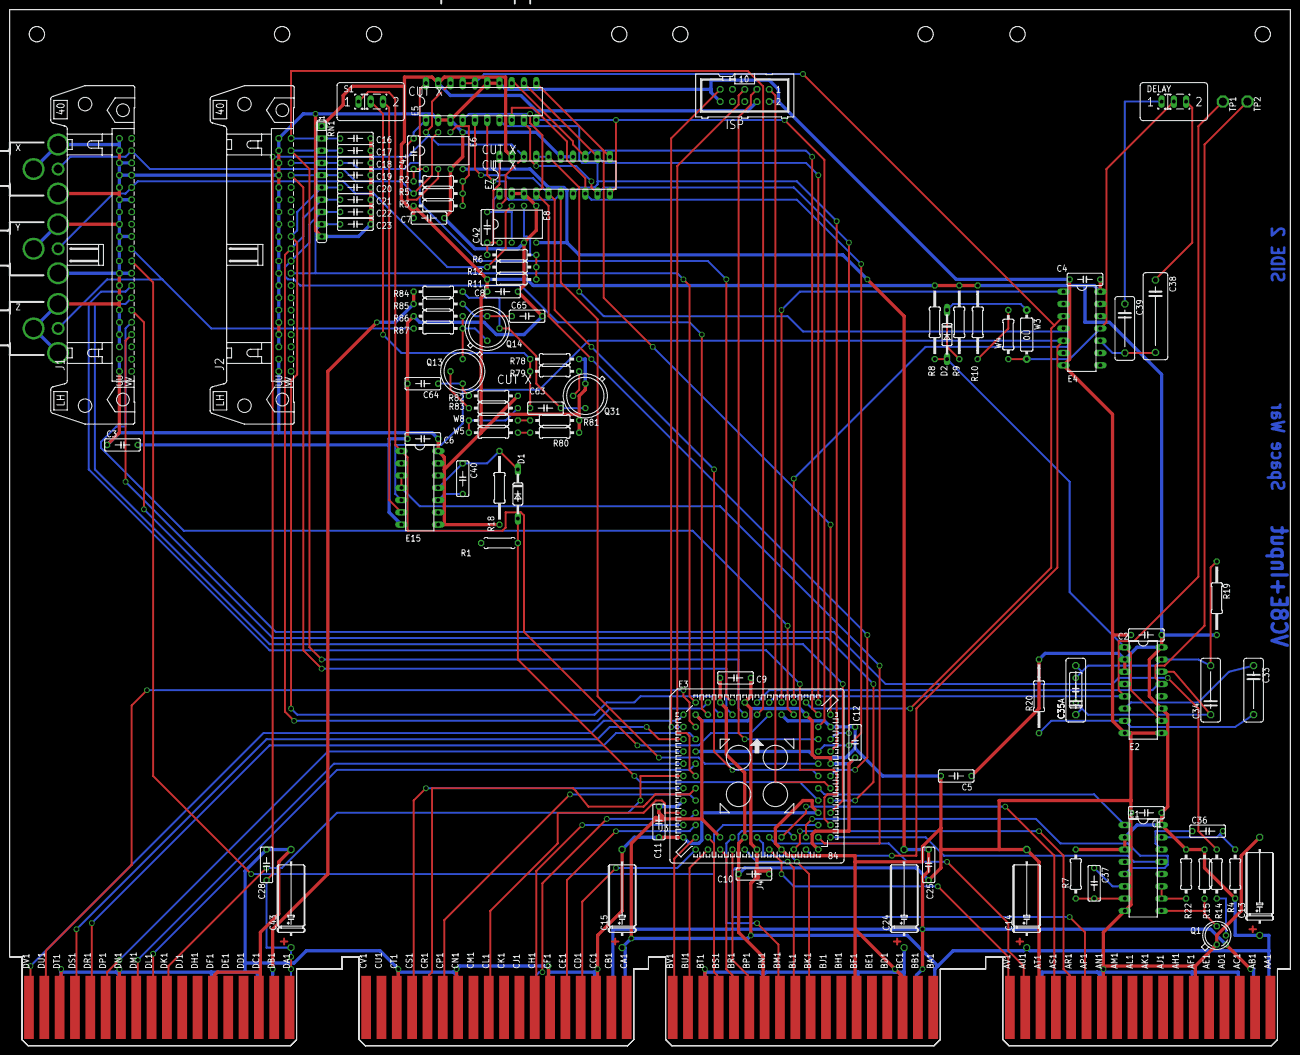
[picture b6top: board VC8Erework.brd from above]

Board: 4 copper layers, 265.3 x 214.6 mm, 103 parts (0 on the bottom side), 115 nets.
